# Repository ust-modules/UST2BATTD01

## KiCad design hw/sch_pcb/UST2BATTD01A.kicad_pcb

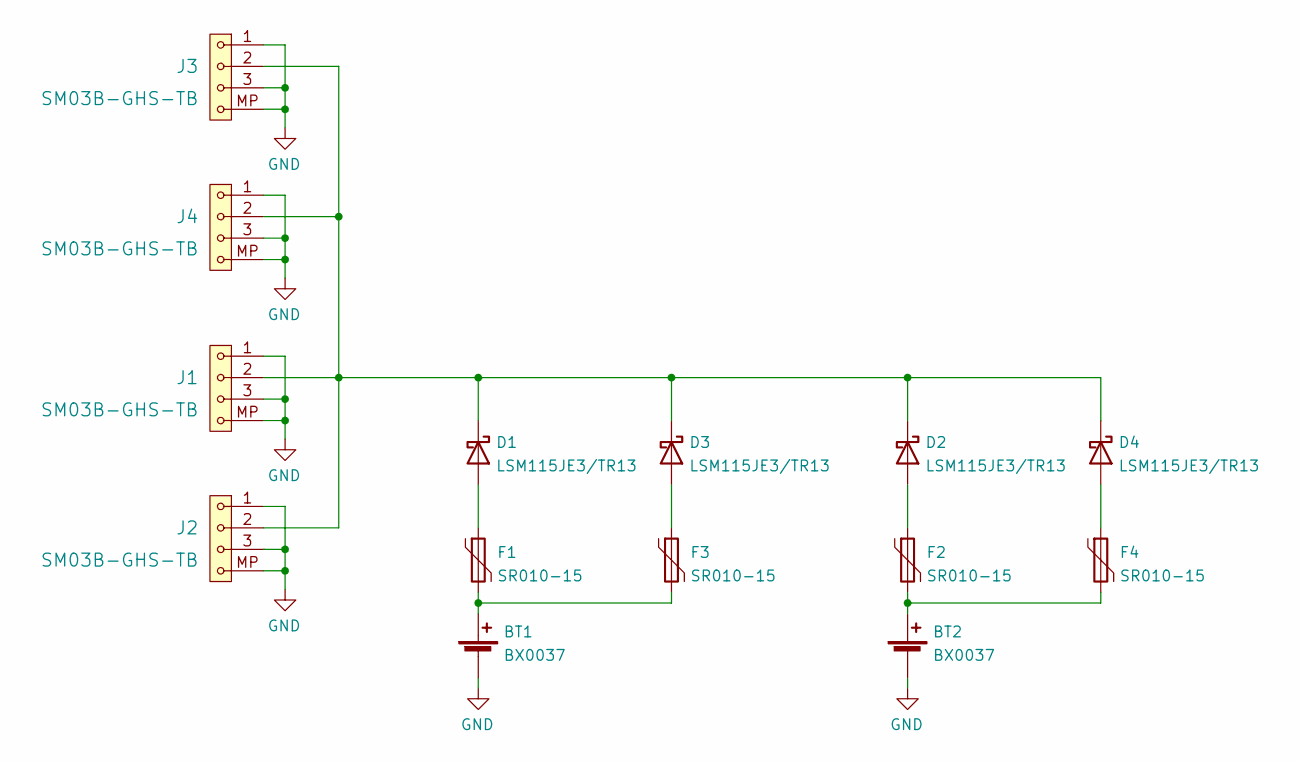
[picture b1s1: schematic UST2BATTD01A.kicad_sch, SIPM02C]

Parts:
BT1, BT2: BX0037
D1, D2, D3, D4: LSM115JE3/TR13; D_SMA_Handsoldering
F1, F2, F3, F4: SR010-15; Fuse_0805_2012Metric_Pad1.15x1.40mm_HandSolder
J1, J2, J3, J4: SM03B-GHS-TB; JST_GH_SM03B-GHS-TB_1x03-1MP_P1.25mm_Horizontal

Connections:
GND: BT1.2 (-), BT2.2 (-), J1.1, J1.3, J1.MP, J2.1, J2.3, J2.MP, J3.1, J3.3, J3.MP, J4.1, J4.3, J4.MP
unnamed: D1.1 (K), D2.1 (K), D3.1 (K), D4.1 (K), J1.2, J2.2, J3.2, J4.2
unnamed: D1.2 (A), F1.1
unnamed: D2.2 (A), F2.1
unnamed: D3.2 (A), F3.1
unnamed: D4.2 (A), F4.1
unnamed: BT1.1 (+), F1.2, F3.2
unnamed: BT2.1 (+), F2.2, F4.2

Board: 2 copper layers, 14 parts (6 on the bottom side), 8 nets, no tracks yet.

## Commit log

2022-07-14 Edit schema
2022-07-15 Edit PCB
2022-07-18 Pridan assets
2022-07-18 Edit kicad_outputs.yml
2022-07-18 Update actions products
